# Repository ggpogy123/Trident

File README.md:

# Trident

A custom, hardware control board featuring a esp32, dual-axis joystick, and three independent SPI displays. 

## Overview
Trident is designed to be a modular, compact interface board. By routing the SPI MOSI, SCK, and LED lines in a daisy chain configuration, the board allows a single ESP32 microcontroller to drive three 2.8 inch TFT LCD screens simultaneously while reading analog inputs from a PS2 style joystick. 

## Visuals

## Hardware Specifications
* **Microcontroller:** ESP32 38-pin Development Board
* **Displays:** 3x 2.8 inch TFT LCDs (ILI9341)
* **Input:** Dual Axis PS2 Analog Joystick Module (KY-023)
* **PCB Specs:** 2-layer FR4, 195.5 x 61.5 mm, 1.6mm thickness

## Key Design Features
* **Wi-Fi Optimization:**  The boundary of the PCB has been cut to ensure that the antenna of the ESP is placed outside the fiberglass. This is done to prevent any kind of interference.
* **Current Handling:** VCC lines are routed with 0.7mm trace widths.
* **Ground Plane:** A copper pour layer has been used to connect all GND points.

## Pin layout

### All Displays

| Pin Name | Connection Type | ESP32 pin | Working |
| :--- | :--- | :--- | :--- |
| **VCC** | Power | 5V | Power |
| **GND** | Ground | GND | Ground|
| **SPI_MOSI**| SPI Data | GPIO 23 | Master Out Slave In |
| **SPI_SCK** | SPI Clock | GPIO 18 | Serial Clock |
| **D_RST** | Shared Reset | GPIO 5 | Hardware reset |
| **LED_BL** | Backlight | GPIO 19 | Backlight |

### Display-Specific Pins

| Screen Number | Chip Select pin | Data/Command pin|
| :--- | :--- | :--- |
| **Display 1 (J1)** | GPIO 21 | GPIO 22 |
| **Display 2 (J2)** | GPIO 27 | GPIO 13 |
| **Display 3 (J3)** | GPIO 15 | GPIO 14 |

### Joystick (J4)

| Joystick Pin | Connection Type | ESP32 pin | Working |
| :--- | :--- | :--- | :--- |
| **VCC** | Power | 5V | Power |
| **GND** | Ground | GND | Ground |
| **JOY_X** | Analog Input | GPIO 36 | X-Axis|
| **JOY_Y** | Analog Input |GPIO 39 | Y-Axis  |
| **JOY_SW** | Digital Input | GPIO 32 | Click |

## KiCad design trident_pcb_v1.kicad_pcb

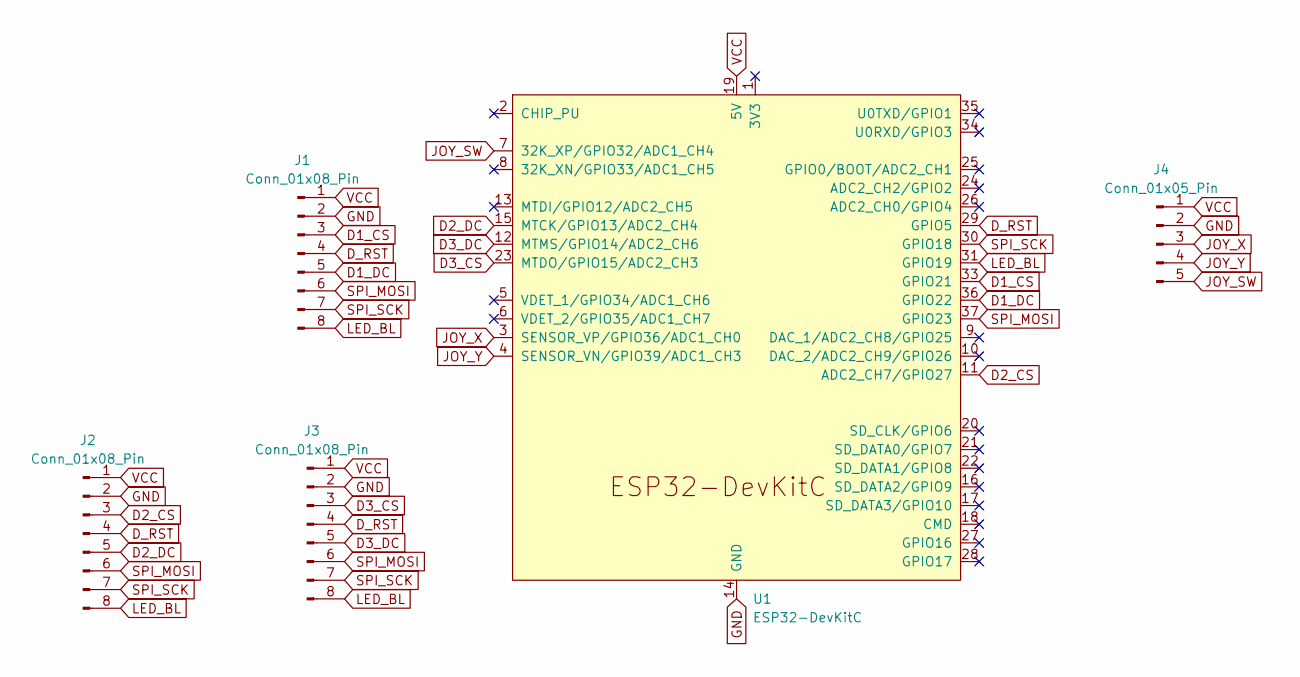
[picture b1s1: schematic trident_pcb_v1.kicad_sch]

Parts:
J1, J2, J3: Conn_01x08_Pin; PinHeader_1x08_P2.54mm_Vertical
J4: Conn_01x05_Pin; PinHeader_1x05_P2.54mm_Vertical
U1: ESP32-DevKitC

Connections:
D1_CS: J1.3, U1.33 (GPIO21)
D1_DC: J1.5, U1.36 (GPIO22)
D2_CS: J2.3, U1.11 (ADC2_CH7/GPIO27)
D2_DC: J2.5, U1.15 (MTCK/GPIO13/ADC2_CH4)
D3_CS: J3.3, U1.23 (MTDO/GPIO15/ADC2_CH3)
D3_DC: J3.5, U1.12 (MTMS/GPIO14/ADC2_CH6)
D_RST: J1.4, J2.4, J3.4, U1.29 (GPIO5)
GND: J1.2, J2.2, J3.2, J4.2, U1.14 (GND), U1.32 (GND), U1.38 (GND)
JOY_SW: J4.5, U1.7 (32K_XP/GPIO32/ADC1_CH4)
JOY_X: J4.3, U1.3 (SENSOR_VP/GPIO36/ADC1_CH0)
JOY_Y: J4.4, U1.4 (SENSOR_VN/GPIO39/ADC1_CH3)
LED_BL: J1.8, J2.8, J3.8, U1.31 (GPIO19)
SPI_MOSI: J1.6, J2.6, J3.6, U1.37 (GPIO23)
SPI_SCK: J1.7, J2.7, J3.7, U1.30 (GPIO18)
VCC: J1.1, J2.1, J3.1, J4.1, U1.19 (5V)

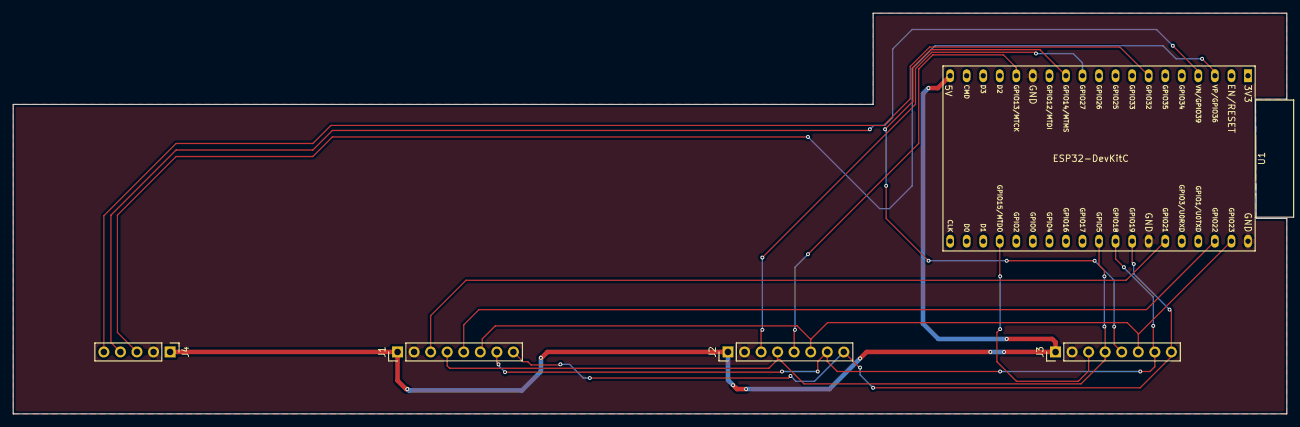
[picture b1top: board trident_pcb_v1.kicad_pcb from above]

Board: 2 copper layers, 195.5 x 61.5 mm, 5 parts (0 on the bottom side), 15 nets.

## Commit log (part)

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2026-06-16 Add schematic file
